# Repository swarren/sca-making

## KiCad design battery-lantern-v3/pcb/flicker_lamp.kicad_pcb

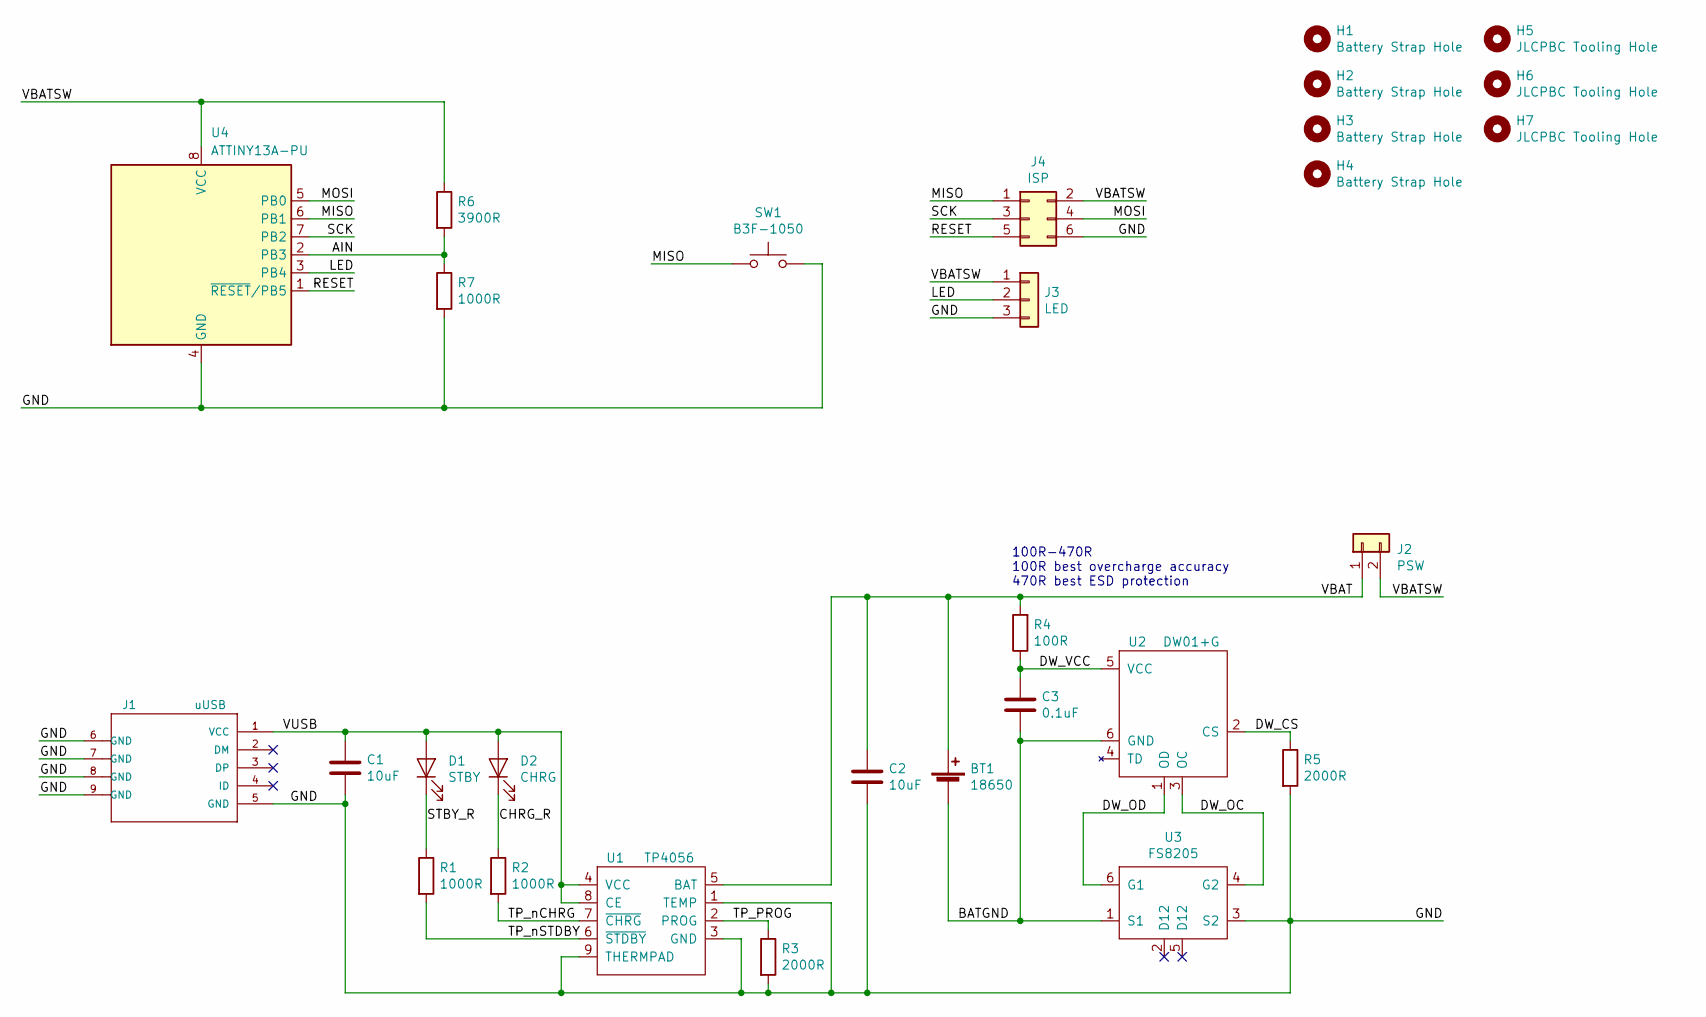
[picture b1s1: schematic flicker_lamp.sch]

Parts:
BT1: 18650; Bat_Clip_Keystone_54_65mm
C1, C2: 10uF; C_0805; MPN CL21A106KAYNNNE; LCSC C15850
C3: 0.1uF; C_0402; MPN CL21B104KCFNCL05B104KO5NNNCNNE; LCSC C1525
D1: STBY; LED_0805; MPN NCD0805R1; LCSC C84256
D2: CHRG; LED_0603; MPN 19-217/GHC-YR1S2/3T; LCSC C72043
H1, H2, H3, H4: Battery Strap Hole; hole-3mm-1.5mm-oval
H5, H6, H7: JLCPBC Tooling Hole; jlcpcb-smt-tooling-hole
J1: uUSB; LCSC-C10418-USB-uB; MPN 920-E52A2021S10100; LCSC C10418
J2: PSW; Pin_Header_Straight_1x02_Pitch2.54mm
J3: LED; Pin_Header_Straight_1x03_Pitch2.54mm
J4: ISP; Pin_Header_Straight_2x03_Pitch2.54mm
R1, R2, R7: 1000R; R_0603; MPN 0603WAF1001T5E; LCSC C21190
R3, R5: 2000R; R_0805; MPN 0805W8F2001T5E; LCSC C17604
R4: 100R; R_0805; MPN 0805W8F1000T5E; LCSC C17408
R6: 3900R; R_0805; MPN 0805W8F3901T5E; LCSC C17614
SW1: B3F-1050; SW_PUSH_6mm
U1: TP4056; LCSC-C16581-TP4056-ESOP-8; MPN TP4056-42-ESOP8; LCSC C16581
U2: DW01+G; SOT-23-6-LCSC; MPN DW01+G; LCSC C14213
U3: FS8205; SOT-23-6-LCSC; MPN FS8205; LCSC C32254
U4: ATTINY13A-PU; DIP-8_W7.62mm

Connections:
/AIN: R6.2, R7.1, U4.2 (PB3)
/BATGND: BT1.2 (-), C3.2, U2.6 (GND), U3.1 (S1)
/CHRG_R: D2.1 (K), R2.1
/DW_CS: R5.1, U2.2 (CS)
/DW_OC: U2.3 (OC), U3.4 (G2)
/DW_OD: U2.1 (OD), U3.6 (G1)
/DW_VCC: C3.1, R4.1, U2.5 (VCC)
/GND: C1.2, C2.2, J1.5 (GND), J1.6 (GND), J1.7 (GND), J1.8 (GND), J1.9 (GND), J3.3, J4.6, R3.2, R5.2, R7.2, SW1.2, U1.1 (TEMP), U1.3 (GND), U1.9 (THERMPAD), U3.3 (S2), U4.4 (GND)
/LED: J3.2, U4.3 (PB4)
/MISO: J4.1, SW1.1, U4.6 (PB1)
/MOSI: J4.4, U4.5 (PB0)
/RESET: J4.5, U4.1 (~RESET~/PB5)
/SCK: J4.3, U4.7 (PB2)
/STBY_R: D1.1 (K), R1.1
/TP_PROG: R3.1, U1.2 (PROG)
/TP_nCHRG: R2.2, U1.7 (~CHRG)
/TP_nSTDBY: R1.2, U1.6 (~STDBY)
/VBAT: BT1.1 (+), C2.1, J2.1, R4.2, U1.5 (BAT)
/VBATSW: J2.2, J3.1, J4.2, R6.1, U4.8 (VCC)
/VUSB: C1.1, D1.2 (A), D2.2 (A), J1.1 (VCC), U1.4 (VCC), U1.8 (CE)

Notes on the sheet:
100R-470R 100R best overcharge accuracy 470R best ESD protection

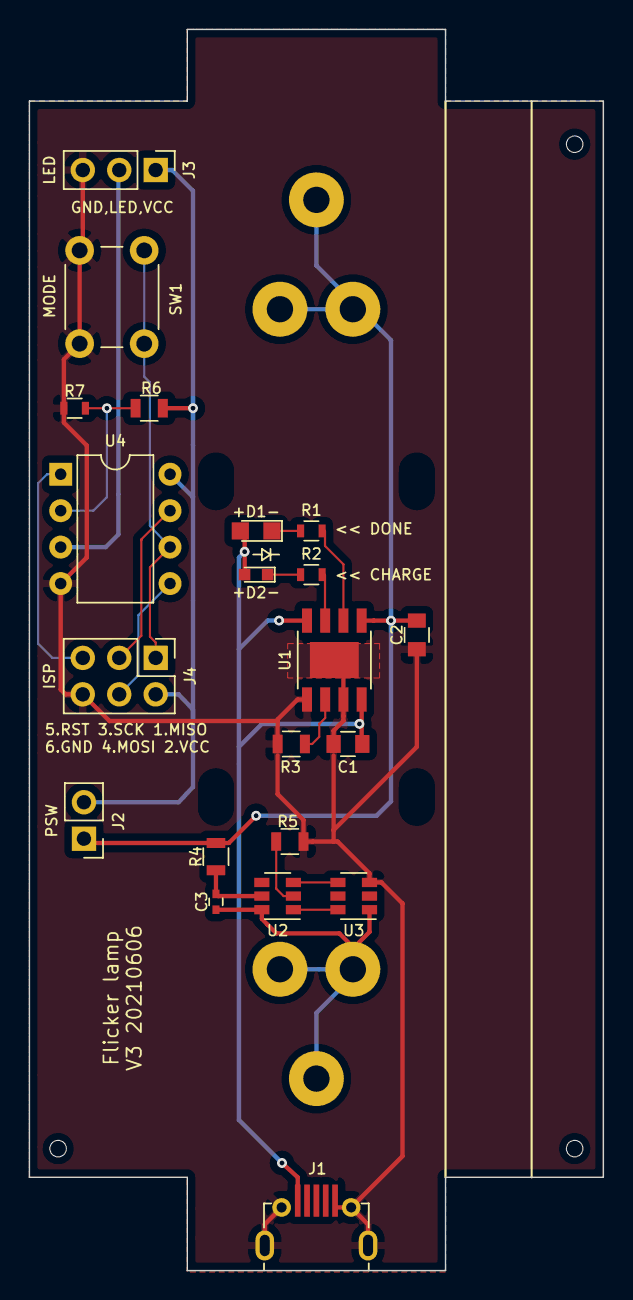
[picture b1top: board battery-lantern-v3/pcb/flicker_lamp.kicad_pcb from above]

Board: 2 copper layers, 40.0 x 86.5 mm, 29 parts (1 on the bottom side), 20 nets.

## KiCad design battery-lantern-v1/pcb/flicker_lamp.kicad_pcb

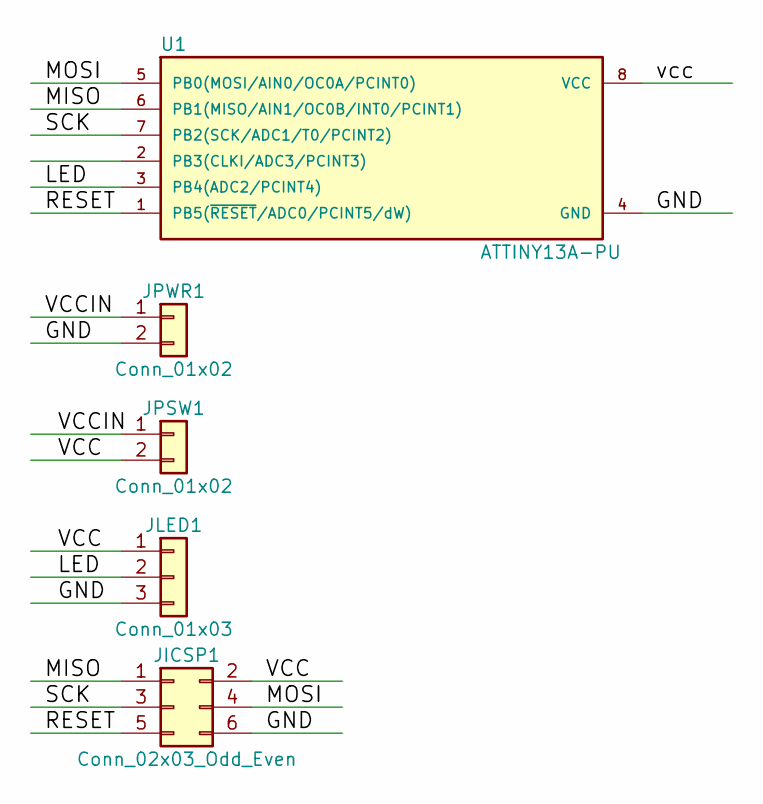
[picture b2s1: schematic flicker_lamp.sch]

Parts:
JICSP1: Conn_02x03_Odd_Even; Pin_Header_Straight_2x03_Pitch2.54mm
JLED1: Conn_01x03; Socket_Strip_Straight_1x03_Pitch2.54mm
JPSW1: Conn_01x02; Socket_Strip_Straight_1x02_Pitch2.54mm
JPWR1: Conn_01x02; Socket_Strip_Straight_1x02_Pitch2.54mm
U1: ATTINY13A-PU; DIP-8_W7.62mm

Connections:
/GND: JICSP1.6, JLED1.3, JPWR1.2, U1.4 (GND)
/LED: JLED1.2, U1.3 (PB4(ADC2/PCINT4))
/MISO: JICSP1.1, U1.6 (PB1(MISO/AIN1/OC0B/INT0/PCINT1))
/MOSI: JICSP1.4, U1.5 (PB0(MOSI/AIN0/OC0A/PCINT0))
/RESET: JICSP1.5, U1.1 (PB5(~RESET~/ADC0/PCINT5/dW))
/SCK: JICSP1.3, U1.7 (PB2(SCK/ADC1/T0/PCINT2))
/VCC: JICSP1.2, JLED1.1, JPSW1.2, U1.8 (VCC)
/VCCIN: JPSW1.1, JPWR1.1

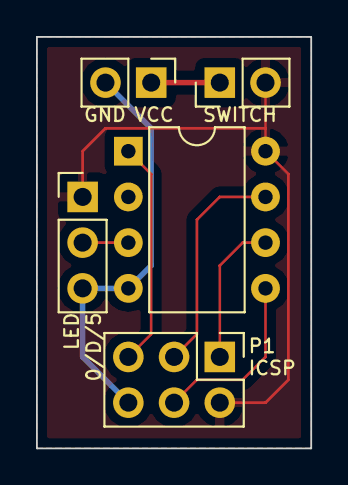
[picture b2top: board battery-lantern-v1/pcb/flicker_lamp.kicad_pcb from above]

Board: 2 copper layers, 15.2 x 22.9 mm, 5 parts (0 on the bottom side), 8 nets.

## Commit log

2019-05-09 Add Lucet fork files
2019-05-18 Add cartwheel lamp BOM
2019-08-16 Add prelimary files for overhead hanging cartwheel lamp
2019-08-16 Lucet forks: Smaller version
    Add smaller lucet fork that'll tesselate into the 24x5" wood I got, and
    update the Lightburn file to use this version, with 4 copies fitting into
    a 12x5" half piece of wood.
2019-09-01 Add pole-mounted cartwheel lamp
    This (as yet untested, and potentially unfinished) design should be
    suitable for mounting around a tent pole (which has a horizontal peg
    sticking through it), or any other vertical pole-like mount.
2019-10-05 Add lots of work!
    - Pole-mounted cartwheel lamp now made (small version).
    - Experimental OpenSCAD version of cartwheel lamp, which will save lots
    of manual Boolean operations when trying out new sizes/designs.
    This hasn't yet been actually manufactured, but generates basically the
    same SVG.
    - Lucet fork Lightburn file power updated, and ???.
2019-10-12 Cartwheel lamp: pole: openscad: automate rendering
    Create a script to run OpenSCAD numerous times to generate each layer.
2019-10-12 Cartwheel lamp: pole: openscad: increase ring size
    This makes the cartwheel almost as large as it can possibly be on a
    600mm x 400mm LASER cutter.
2019-10-12 Cartwheel lamp: pole: openscad: Add LightBurn files
2019-10-12 Cartwheel lamp: pole: openscad: tweak pole sizes
2019-10-17 Cartwheel lamp: pole: file re-org and README
    - Move Inkscape files into a sub-directory.
    - Add a complete README for this version of the lamp.
    - Add lots of build log images!
2019-10-17 Cartwheel lamp: pole: fix README
    Fill in the first section correctly! It was previously cut/paste from a
    different README.
2019-10-18 Battery lamp v2: Initial design
2019-10-25 Battery lamp v2
    Enhancements following making the first rev.
    - Increase dowel diameter to 1/4" for sturdiness.
    - Move dowels out to give more interior space.
    - Add rope holes in top layer.
    - Split top into 3 layers, for next point.
    - Add cutouts for plastic sheeting for light diffusion.
2019-11-10 Battery lamp code minor script fixes
    - Add build script.
    - Move flash script.
2019-11-10 Battery lamp v2: Add PCB design
    Add a PCB design that also acts as the vertical riser in the lamp's core.
    This design should also make wire routing and soldering much simpler.
    The LED mount will need to be updated later to accept a thinner riser,
    and perhaps update the wire routing cut-out.
2019-11-17 Battery lantern v2: Window layout optimization
    Make all the windows adjacent. This allows slightly better optimization
    of the LASER path, and avoids leaving behind lots of thin plastic strips
    between the cut-out windows.
2019-11-20 Battery lamp v2: move rope holes
    To make more space on the top for engraving:
    - Rotate rope holes 30 degrees, to place them near the vertical poles.
    - Make rope hole placement wider.
2019-11-23 Battery lamp v2: Design LED mount in OpenSCAD
    The cutout for the wiring might need some tweaks, but this basically
    works. The internal holes in the top layer hold paper clips that hold
    the LED strip in place while the glue dries.
2019-11-23 Battery lamp v2: Gerber files
    - Add aux origin to PCB for Gerber generation.
    - Add Gerber files sent to fab.
2019-11-25 Battery lamp v2: Tweak LED mount wire routing cutout
    This should allow smoother bending of the wire.
2019-11-26 Battery lamp v2: Add end stops to base rotation
    This allows the lamp internals to be rotated almost 180 degrees up to the
    endstop, rather than just rotating 90 degrees. This makes it less likely
    the internals will rotate out of the slot.
2019-11-26 Battery lamp v2: space out window cuts
    When the windows share edges, they can drop out of the material before all
    edges have been cut, leaving uncut edges. Space them out again to avoid
    this.
2019-12-09 Battery lamp v2: Add manufacturing files
    - Add Lightburn files for LASER cutting the lamp
    - Add PCB design sent to seeedstudio.
    Note: base-layer3-array.lbrn manually re-arrayed using LightBurn after
    adding "Design by Ulric" logo.
2020-01-09 Battery lantern: add flash loop script
    This allows quick and easy mass flashing.
2020-01-21 Battery lantern: misc edits
    - Add some notes about LASER cutter settings and TODO items.
    - Resave Lightburn files in newer version of SW. No semantic change.
2020-01-21 Battery lantern v2: PCB tweaks for v2A
    - Silscreen LED holder glue area on both sides of PCB.
    - Tabs on side for LED holder to sit on and align easily.
    - Pull back copper pour near power connectors to avoid possibility of
    shorts through the solder mask by bent over wires.
    - Widen slightly to avoid hot glue getting in power connector holes.
    - Spread copper pours over bottom of PCB.
2020-01-22 Battery lantern v2: PCB origin tweak
    This change makes more Gerber viewers correctly align the Gerber layers
    with the drill file. This misalignment might have delayed production at
    Seeedstudio last time, although they didn't ask about it.
2020-02-02 Battern lantern: fix build.sh, add custom color
2020-02-11 Battery lantern v2: Add "packed" cutting layout
    This layout fits 4 entire lanterns into a single wood sheet. This will
    allow fewer lanterns to be made in a single batch, and a faster path to
    perform enough cutting to make at least some complete lanterns.
2020-02-12 Add files for a double-walled box
2020-03-15 Add box files for the boxes I've made
    I've manufactured 2 "real" (i.e. non-test) versions of the box. These
    are the exact files/dimensions used for those.
2020-08-23 Add files for single-walled box, with handles and internal support
2020-08-25 Topless box: Add vertical support beams
2020-10-04 Add Medingen click table model (WIP?)
2020-10-08 Medingen: rework beam & pegs, add middle leg
2020-11-15 Add naalbinding needles
2021-06-07 Battery lantern v3 PCB
2021-06-08 Lantern v3: gitignore fp-info-cache
2021-06-08 Lantern v3: Archive uploaded BOM to gerber directory
2021-06-22 Lantern v3: code
    Relative to v1 code:
    - Add low battery detection and cutout.
    - ADC for low battery detection.
    - Flash red on low battery for a while.
    - Power off LEDs and CPU after notification.
    - Support multiple color/brightness levels.
2021-06-22 Lantern v3: OpenSCAD files
    Enhancements v.s. v2:
    - Vertical rods blind at the top for cleaner look (untested so far).
    - Body's core hole slightly tigher tolerance.
    - Core re-designed around new PCB. PCB is integral to structure rather
    than being an add-on.
    - All layers of core aligned by rods for tighter alignment.
2022-08-29 Water container box
